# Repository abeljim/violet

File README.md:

# Violet

Small Vector Network Analyzer

## Getting Started

This repository is made up of two sections software and hardware. View folders for more information.
 
## Authors 

* **Abel Jimenez** - *Initial work*

## Licsense

This project is licensed under the GPLv2 License -- see the [LICENSE.md](LICENSE.md) file for details 

## Acknowledgments

* TODO

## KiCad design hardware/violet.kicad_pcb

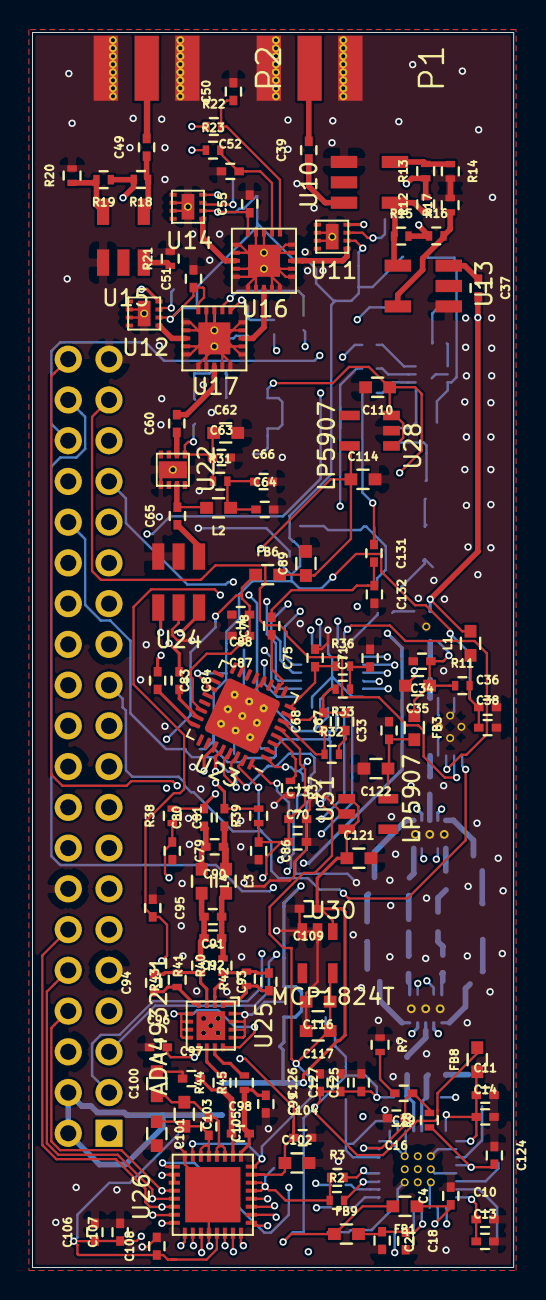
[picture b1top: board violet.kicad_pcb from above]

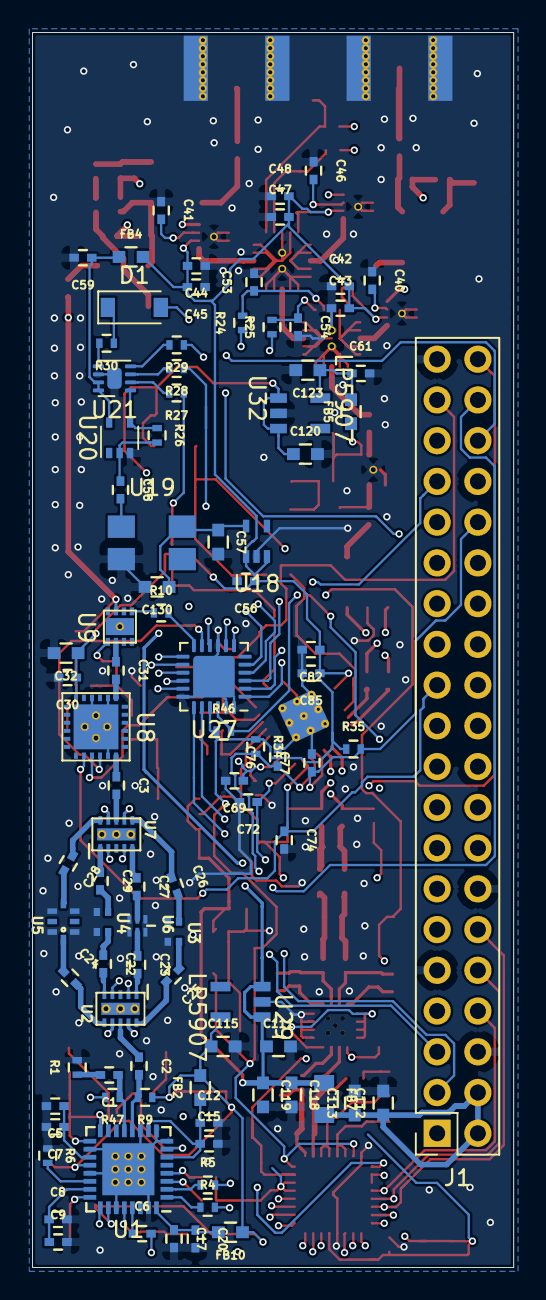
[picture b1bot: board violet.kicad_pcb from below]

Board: 4 copper layers, 30.0 x 77.0 mm, 227 parts (95 on the bottom side), 164 nets.

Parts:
C1, C2, C3, C25, C26, C31, C37, C39, C49, C60, C65, C78, C83, C84: 1n; C_0402b
C4, C5, C8, C10, C14, C15, C17, C18, C22, C29, C91, C97, C99, C125: 100p; C_0402b
C6, C38, C58, C66, C70, C85, C88: 10n; C_0402b
C7, C9, C11, C12, C13, C20, C21, C33, C34, C56, C59, C61, C63, C79, C80, C81, C86, C95, C96, C104, C105, C106, C107, C108, C109, C127: 100n; C_0402b
C16: 2.7n; C_0402b
C19: 47n; C_0402b
C23, C24, C27, C28, C36, C64, C73, C126: 10p; C_0402b
C30: 1000p; C_0402b
C32, C57, C100, C101, C110, C111, C114, C115, C120, C121, C122, C123: 1u; C_0603b
C35, C62, C89, C112, C113, C116, C117, C118, C119: 10u; C_0603b
C40, C41, C46: 4.9p; C_0402b
C42, C44, C47: 0.5p; C_0402b
C43, C45, C48: 4.5p; C_0402b
C50, C52, C53, C54: 2p; C_0402b
C51, C55: 0.1u; C_0402b
C67: 180p; C_0402b
C68: 8.2p; C_0402b
C69, C72, C74, C76, C77, C82, C87, C131: 33p; C_0402b
C71, C75: 330p; C_0402b
C90, C93, C94: 18p; C_0402b
C92: 36p; C_0402b
C98: 220p; C_0402b
C102, C103: 2.2u; C_0603b
C124: 680p; C_0402b
C130: 0.1u; C_0603b
C132: 47p; C_0402b
D1: DIODE; D_SOD-123
FB1, FB2, FB3, FB4, FB5, FB6, FB8, FB9, FB10: Ferrite_Bead_Small; C_0603b
FB7: Ferrite_Bead; C_0805b
J1: Conn_02x20_Odd_Even; PinSocket_2x20_P2.54mm_Vertical_Centered_Anchor
L1, L2: 100n; C_0603b
L3, L4: 1u; C_0603b
P1, P2: SMA; CONSMA003.062
R1, R12, R13, R14, R15, R16, R17, R18, R19, R20, R21, R38, R39: 49.9; R_0402b
R2, R3, R34, R35, R46: 10k; R_0402b
R4, R5, R10: 100; R_0402b
R6: 4.7k; R_0402b
R7: 360; R_0402b
R8, R40, R41: 1k; R_0402b
R9, R44, R45, R47: 50; R_0402b
R11, R31: 1.8; R_0402b
R22, R23, R24, R25: 5k; R_0402b
R26: 1M; R_0402b
R27, R28, R29, R30: 33; R_0402b
R32: 22k; R_0402b
R33, R36: 470; R_0402b
R37: 51k; R_0402b
R42, R43: 3.3k; R_0402b
U1: ADF4351; LFCSP-32-1EP_5x5mm_P0.5mm_EP3.25x3.25mm
U2, U7: SKY13322-375LF; MLPD-10
U3, U4: LP0603; LP0603A0902
U5: 5515LP15A730
U6: 3550LP14A300
U8: QPC6614TR13; QPC6614
U9: TRF37A73; DFN-8-1EP_2x2mm_Pitch0.5mm
U10, U13, U15: RFXF9503; S20
U11, U12, U14: F2910
U16, U17: F2913
U18: MIC5366 3.0v; SC-70-5
U19: CVT32-10.000
U20: NC7SVU04P5X; SOT-353_SC-70-5
U21: NB3N551MN; DFN-8-1EP_2x2mm_P0.5mm_EP0.9x1.3mm
U22: TRF37A75; DFN-8-1EP_2x2mm_Pitch0.5mm
U23: RFFC5072; QFN-32-1EP_5x5mm_P0.5mm_EP3.65x3.65mm_ThermalVias
U24: TCM1-63AX+
U25: ADA4932-1; VQFN-16
U26: LTC224X; QFN-32_5mm_x_5mm_LTC224X
U27: TCA9555RGER; QFN-24-1EP_4x4mm_P0.5mm_EP2.6x2.6mm
U28, U29, U31, U32: LP5907; SOT-23-5
U30: MCP1824T; SOT-23-5

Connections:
/3V3D: C30.1, C32.1, C42.2, C43.2, C44.2, C45.2, C47.2, C48.2, C51.1, C55.1, C56.1, C82.1, C85.1, C106.1, C107.1, C108.1, C116.1, C117.1, FB4.2, R2.1, R3.1, R34.1, R35.1, R46.1, U8.18, U11.6, U12.6, U14.6, U16.20, U17.20, U18.1, U18.3, U23.19, U26.7, U26.21, U26.29, U26.30, U26.32, U27.21, U30.5
/3V3_RX: C89.1, C95.2, C114.1, FB6.2, U25.5, U25.6, U25.7, U25.8, U25.12, U28.5
/3V3_RX_AMP: C61.1, C123.1, FB5.2, U32.5
/3V3_TX: C115.1, C125.1, C126.1, C127.1, FB1.2, FB2.2, FB8.2, FB9.1, FB10.1, R9.1, R47.2, U29.5
/3V3_TX_AMP: C33.1, C122.1, FB3.2, U31.5
/5VP: C112.1, C113.1, FB7.2, J1.2, J1.4
/ADC/VCM: C96.2, C102.1, C104.1, U25.9, U26.31
/ADC_OF: J1.27, U26.28
/ADC_SHDN: U26.10, U26.11, U27.17
/ATTN_DATA: J1.37, U8.3
/ATTN_LE: U8.4, U27.11
/ATTN_PWDN: R10.2, U27.12
/CLK_ADC: R29.1, U26.9
/CLK_LO: C131.1, R27.1
/CLK_MC: D1.2, J1.36
/CLK_TX: C6.2, R28.1
/D0: J1.8, U26.12
/D1: J1.10, U26.13
/D2: J1.12, U26.14
/D3: J1.16, U26.15
/D4: J1.18, U26.16
/D5: J1.7, U26.17
/D6: J1.11, U26.18
/D7: J1.13, U26.19
/D8: J1.15, U26.22
/D9: J1.19, U26.23
/D10: J1.21, U26.24
/D11: J1.22, U26.25
/D12: J1.24, U26.26
/D13: J1.26, U26.27
/DET: C49.2, P2.1
/DUT: C39.2, P1.1
/EXP_INT: J1.33, R46.2, U27.22
/FB_1: U2.4, U7.2, U27.13
/FB_2: U2.2, U7.4, U27.14
/FB_3: U2.7, U7.9, U27.15
/FB_4: U2.9, U7.7, U27.16
/Filter Bank/RF_IN: C2.1, U2.8
/Filter Bank/RF_OUT: C3.2, U7.8
/IF AMP/ADC+: C98.2, C99.1, R45.1, U26.1
/IF AMP/ADC-: C97.2, C98.1, R44.1, U26.2
/IF AMP/IF+: C81.1, C90.1, L3.1
/IF AMP/IF-: C80.1, C90.2, L4.1
/Power/5V: C109.1, C110.1, C111.1, C118.1, C119.1, C120.1, C121.1, FB7.1, U28.1, U28.3, U29.1, U29.3, U30.1, U31.1, U31.3, U32.1, U32.3
/RF_RX: C60.2, U17.8
/RX Mixer/3V3A: C70.1, C73.1, C79.1, C86.1, C87.1, C88.1, FB6.1, R38.1, R39.1, U23.5, U23.22
/RX Mixer/LFILT1: C68.1, R32.1, U23.6
/RX Mixer/LFILT2: C67.2, C68.2, R33.2, U23.7
/RX Mixer/LFILT3: C75.1, R36.1, U23.8
/RX Mixer/RF_IN: C65.1, U24.3
/RX_DATA: C72.1, J1.40, U23.32
/RX_EN: C69.1, U23.1, U27.10
/RX_ENX: C76.1, J1.38, R34.2, U23.30
/RX_RST: C77.1, J1.32, R35.2, U23.29
/SCL: J1.5, U27.19
/SDA: J1.3, U27.20
/SPI_CLK: C74.1, J1.23, R4.2, U8.2, U23.31
/SW1: C41.2, U11.7, U27.8
/SW2: C46.2, U14.7, U27.4
/SW3: C40.2, U12.7, U27.1
/SW4: R23.1, U27.2
/SW5: R22.1, U27.3
/SW6: R25.1, U27.5
/SW7: R24.1, U27.7
/Switches/A: R12.2, R13.1, U14.8
/Switches/A_OUT: U14.5, U16.3
/Switches/B: R18.2, R19.1, U12.8
/Switches/B_OUT: U12.5, U17.3
/Switches/RF_IN: C37.1, U13.3
/Switches/RX1: R15.2, R16.1, U11.8
/Switches/RX1_OUT: U11.5, U16.13
/TX_CE: J1.29, R3.2, U1.4
/TX_DATA: J1.31, R5.2
/TX_LD: J1.35, U1.25
/TX_LE: J1.28, R2.2, U1.3
/Transmitter /RF_OUT_N: C1.1, R47.1, U1.13
/Transmitter /RF_OUT_P: C2.2, R9.2, U1.12
/Transmitter Amp/RF_IN: C3.1, U8.6
GND: C4.2, C5.2, C7.2, C8.2, C9.2, C10.2, C11.2, C12.2, C13.2, C14.2, C15.2, C16.2, C17.2, C18.2, C20.2, C21.2, C30.2, C32.2, C33.2, C34.2, C35.2, C36.2, C38.2, C40.1, C41.1, C42.1, C43.1, C44.1, C45.1, C46.1, C47.1, C48.1, C50.2, C51.2, C52.1, C53.2, C54.2, C55.2, C56.2, C57.2, C59.2, C61.2, C62.2, C63.2, C64.2, C66.2, C69.2, C70.2, C71.2, C72.2, C73.2, C74.2, C75.2, C76.2, C77.2, C79.2, C82.2, C85.2, C86.2, C87.2, C88.2, C89.2, C95.1, C96.1, C97.1, C99.2, C100.2, C101.2, C102.2, C104.2, C106.2, C107.2, C108.2, C109.2, C110.2, C111.2, C112.2, C113.2, C114.2, C115.2, C116.2, C117.2, C118.2, C119.2, C120.2, C121.2, C122.2, C123.2, C124.1, C125.2, C126.2, C127.2, C130.2, C132.2, J1.6, J1.9, J1.14, J1.20, J1.25, J1.30, J1.34, J1.39, P1.2, P2.2, R1.2, R6.1, R7.1, R14.2, R17.2, R20.2, R21.2, R37.2, U1.8, U1.9, U1.11, U1.18, U1.21, U1.27, U1.31, U1.33, U2.EP, U3.3, U3.4, U4.3, U4.4, U5.1, U5.3, U5.5, U5.7, U6.1, U6.3, U6.4, U6.6, U7.EP, U8.5, U8.14, U8.16, U8.EP, U9.9, U10.1, U11.2, U11.3, U11.EP, U12.2, U12.3, U12.EP, U13.1, U14.2, U14.3, U14.EP, U15.1, U16.1, U16.2, U16.4, U16.5, U16.6, U16.7, U16.9, U16.10, U16.11, U16.12, U16.14, U16.15, U16.18, U16.19, U16.EP, U17.1, U17.2, U17.4, U17.5, U17.6, U17.7, U17.9, U17.10, U17.11, U17.12, U17.14, U17.15, U17.18, U17.19, U17.EP, U18.2, U19.2, U20.3, U21.6, U21.9, U22.5, U22.9, U23.12, U23.33, U24.1, U24.2, U24.5, U25.13, U25.14, U25.15, U25.16, U25.EP, U26.8, U26.20, U26.EP, U27.9, U27.18, U27.23, U27.24, U27.25, U28.2, U29.2, U30.2, U30.3, U31.2, U32.2
unnamed: C1.2, R1.1
unnamed: C4.1, FB1.1, U1.26
unnamed: C5.1, C7.1, U1.19
unnamed: C6.1, U1.29
unnamed: C8.1, C9.1, U1.23
unnamed: C10.1, C13.1, U1.24
unnamed: C11.1, C14.1, FB8.1, U1.16, U1.17
unnamed: C12.1, C15.1, FB2.1, U1.6, U1.10
unnamed: C16.1, C19.1, R8.2, U1.7
unnamed: C17.1, C20.1, FB10.2, U1.32
unnamed: C18.1, C21.1, FB9.2, U1.28
unnamed: C19.2, R7.2
unnamed: C22.1, U4.1
unnamed: C22.2, U2.5
unnamed: C23.1, U6.2
unnamed: C23.2, U2.1
unnamed: C24.1, U5.8
unnamed: C24.2, U2.6
unnamed: C25.1, U3.1
unnamed: C25.2, U2.10
unnamed: C26.1, U7.6
unnamed: C26.2, U3.2
unnamed: C27.1, U7.5
unnamed: C27.2, U6.5
unnamed: C28.1, U7.10
unnamed: C28.2, U5.4
unnamed: C29.1, U7.1
unnamed: C29.2, U4.2
unnamed: C31.1, U9.2
unnamed: C31.2, U8.13
unnamed: C34.1, C35.1, FB3.1, R11.1, U9.1
unnamed: C36.1, C38.1, L1.1, R11.2
unnamed: C37.2, L1.2, U9.7
unnamed: C39.1, U10.3
unnamed: C49.1, R18.1, U15.4
unnamed: C50.1, R22.2, U16.16
unnamed: C52.2, R23.2, U16.17
unnamed: C53.1, R24.2, U17.17
unnamed: C54.1, R25.2, U17.16
unnamed: C58.1, R26.2, U20.2
unnamed: C58.2, U19.3
unnamed: C59.1, FB4.1, U20.5, U21.7, U21.8
unnamed: C60.1, U22.2
unnamed: C62.1, C63.1, FB5.1, R31.1, U22.1
unnamed: C64.1, C66.1, L2.1, R31.2
unnamed: C65.2, L2.2, U22.7
unnamed: C67.1, R32.2
unnamed: C71.1, R33.1, R36.2
unnamed: C78.1, U23.10
unnamed: C80.2, R38.2, U23.28
unnamed: C81.2, R39.2, U23.27
unnamed: C83.1, U24.4
unnamed: C83.2, U23.24
unnamed: C84.1, U24.6
unnamed: C84.2, U23.23
unnamed: C91.1, C92.1, L3.2, R40.2
unnamed: C91.2, C92.2, L4.2, R41.2
unnamed: C93.1, R42.1, U25.1
unnamed: C93.2, R40.1, R42.2, U25.2
unnamed: C94.1, R43.1, U25.4
unnamed: C94.2, R41.1, R43.2, U25.3
unnamed: C100.1, C103.1, C105.1, U26.3, U26.4
unnamed: C101.1, C103.2, C105.2, U26.5, U26.6
unnamed: C124.2, R8.1, U1.20
unnamed: C57.1, C130.1, U18.5, U19.4
unnamed: C78.2, C131.2, C132.1
unnamed: D1.1, R30.1
unnamed: R4.1, U1.1
unnamed: R5.1, U1.2
unnamed: R6.2, U1.22
unnamed: R10.1, U9.5
unnamed: R12.1, R15.1, U10.4, U13.4
unnamed: R13.2, R14.1, U10.5
unnamed: R16.2, R17.1, U13.5
unnamed: R19.2, R20.1, U15.5
unnamed: R21.1, U15.3
unnamed: R26.1, U20.4, U21.1
unnamed: R27.2, U21.2
unnamed: R28.2, U21.3
unnamed: R29.2, U21.4
unnamed: R30.2, U21.5
unnamed: R37.1, U23.4
unnamed: R44.2, U25.10
unnamed: R45.2, U25.11
unnamed: U16.8, U17.13

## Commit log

2019-08-06 added gitignore
2019-10-10 .gitignore fix
2019-10-10 software file
2019-10-23 qpc6614 drivers
2019-11-06 updated csv file
2019-11-06 started adc driver
2019-11-07 added more adc code
2019-11-21 worked on tca9555
2019-11-25 Added more functionality to tca955
2019-11-25 most of tca9555 code completed
2019-12-04 added pyadf4351
2019-12-05 restrucure files
2019-12-09 started meson build
2019-12-09 restructred meson builds
2019-12-10 fixed qpc6614
2020-01-07 updated readme and added licsense
2020-01-07 fixed readme
2020-01-07 spelling fix
2020-01-07 added builddir to gitignore
2020-01-07 removed build
2020-01-17 added software readme
2020-01-20 added build script
2020-01-20 added vscode stuffs
2020-01-20 got base driver to build with bit-banging
2020-01-20 added cpp guard for c files
2020-01-20 renamed pin for clarity
2020-01-20 added some code to main for testing
2020-01-21 removed unnecessary reg and change 5072 to 5071
2020-01-28 kernel module
2020-01-28 ltc224x main
